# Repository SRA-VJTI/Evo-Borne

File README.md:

# Evoborne
This repository focuses on building an open-source _morphobot_
Autonomous human-friendly Multi-Terrain Scaling Vehicle

## Table of Contents
- Introduction
- Features
- Use Case

## Introduction
EvoBorne is a versatile multi-terrain modular robot designed to adapt to various surface and aerial environments, morphing its structure to meet the demands of its surroundings. It operates as a wheeled robot on land, navigating diverse terrains with speed and agility, and seamlessly transforms into a drone when flight is required. Equipped with advanced mapping techniques and a dynamic morphing capability, EvoBorne can autonomously switch between ground and aerial modes, optimizing performance for complex tasks such as search and rescue, environmental monitoring, and exploration. Its robust, customizable design makes it a powerful tool for overcoming challenging environments.

## Features
### Modular & Adaptive Design

EvoBorne's modular design allows it to easily adapt its structure for different environments and tasks. The design is such that it can be reconfigured, enhancing its versatility and enabling quick transitions between ground and aerial modes.

### Powerful Processing Capabilities

EvoBorne is equipped with powerful processors such as the Jetson Nano that can handle real-time navigation. These capabilities allow the robot to execute complex tasks efficiently, supporting advanced terrain mapping and path-finding operations.

### Multiple Operational Modes

EvoBorne can seamlessly switch between multiple operational modes, functioning as a wheeled robot on land and transforming into a drone when aerial mobility is needed. This flexibility allows it to tackle a variety of tasks in diverse environments.

### Efficient Actuation with Custom ESP32 based custom PCB

The robot's actuation system is controlled by a custom ESP32-based development board, providing efficient and precise control over movement and transformations. This tailored setup enhances responsiveness and overall performance.

### Robust & Precise Flight Control

EvoBorne uses a SpeedyBee flight controller for robust and precise flight control, ensuring stable and reliable aerial operations. This system provides advanced control algorithms that enhance the robot's agility and accuracy during flight.

## Use Case
- EvoBorne is designed to enhance **search and rescue operations** by navigating difficult environments autonomously, using advanced technology to interact with people, and ultimately improving emergency response efficiency. By addressing these issues, EvoBorne could play a vital role in saving lives.
- EvoBorne represents a significant advancement in emergency response technology. Its innovative design and cutting-edge features aim to improve how we handle crises, enabling faster and more efficient assistance in difficult conditions. By reducing the time required to locate and help individuals in danger, EvoBorne could be pivotal in saving lives. Its flexibility and technological sophistication not only make it a valuable tool for rescuers but also push the boundaries of what robots can achieve in real-world scenarios.

## Frameworks & Technologies
- ESP-IDF
- Betaflight
- SolidWorks
- ROS

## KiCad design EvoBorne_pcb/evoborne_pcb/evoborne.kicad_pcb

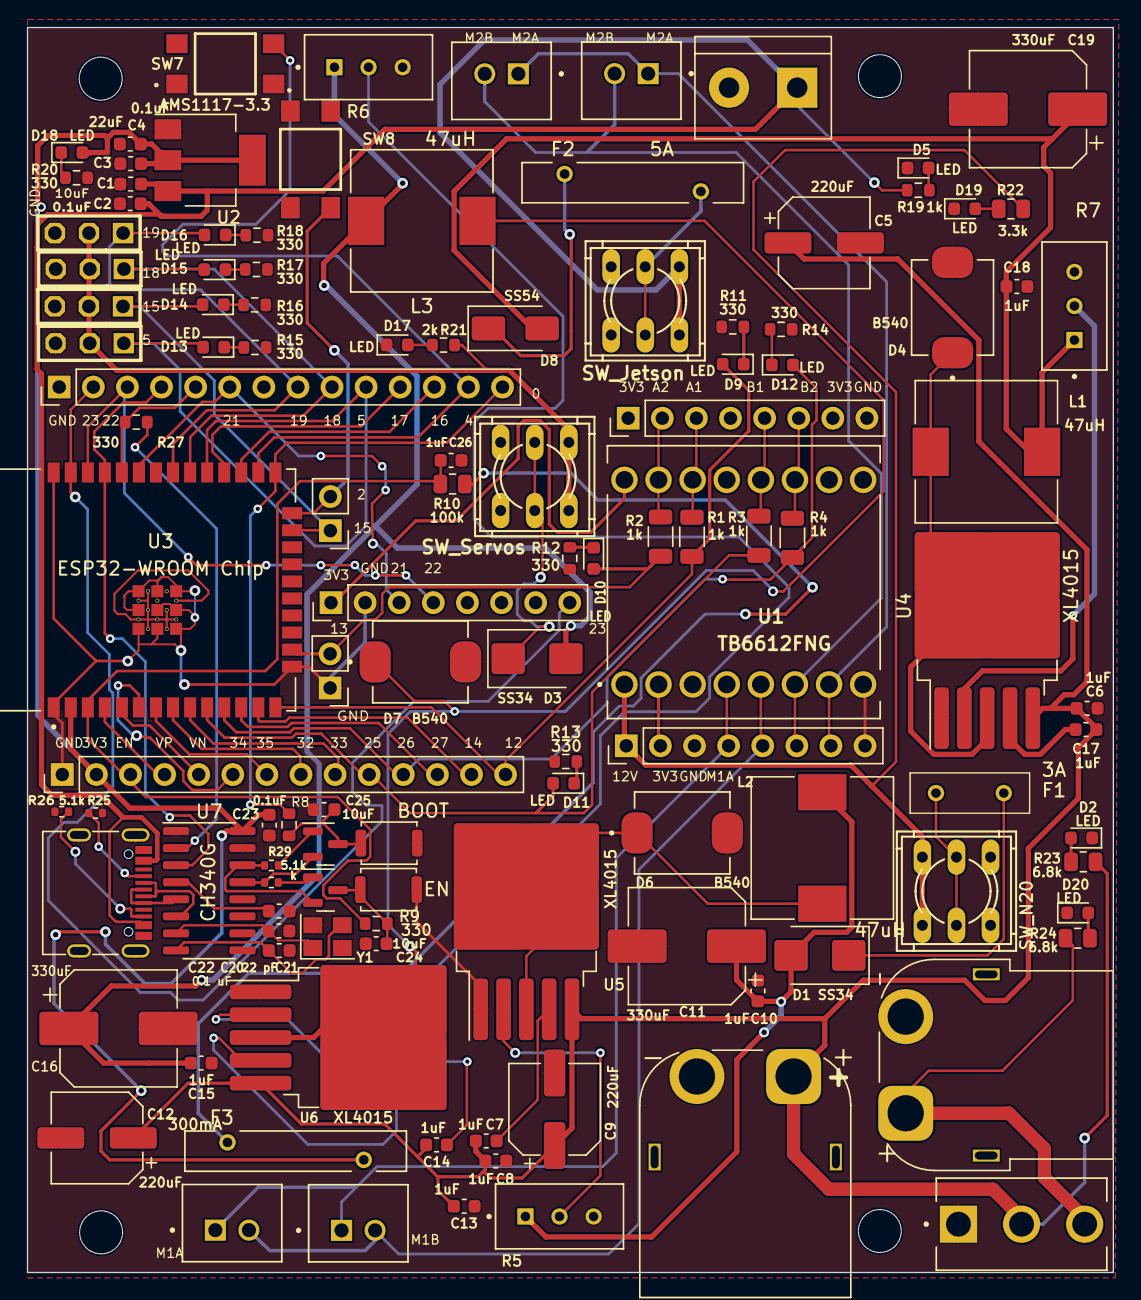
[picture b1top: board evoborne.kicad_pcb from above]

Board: 2 copper layers, 80.9 x 92.7 mm, 122 parts (0 on the bottom side), 88 nets.

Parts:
C1, C24, C25: 10uF; C_0603_1608Metric
C2, C4, C23: 0.1uF; C_0603_1608Metric
C3: 22uF; C_0603_1608Metric
C5, C9, C12: 220uF; CP_Elec_6.3x7.7
C6, C7, C8, C10, C13, C14, C15, C17, C18, C26: 1uF; C_0603_1608Metric
C11, C16, C19: 330uF; CP_Elec_8x10.5
C20, C21: 22 pF; C_0603_1608Metric
C22: 0.1 uF; C_0603_1608Metric
D1, D3: SS34; D_SMB
D2, D5, D9, D10, D11, D12, D13, D14, D15, D16, D17, D18, D19, D20: LED; LED_0603_1608Metric
D4, D6, D7: B540; Diode B540
D8: SS54; D_SMA
F1: 3A; RUEF160
F2: 5A; 5A PTC Fuse RGEF500
F3: 300mA; 1A PTC Fuse RXEF050
H1, H2, H3, H4: MountingHole; MountingHole_3.2mm_M3
J1, J2, J3, J4: B2B-XH-A_LF__SN_; 2 Pin JST
J5, J6, J7, J8: Conn_01x03_Pin; Headers 1X03
J9: XT60; AMASS_XT60PW-M_1x02_P7.20mm_Horizontal
J10: XT60; AMASS_XT60PW-F_1x02_P7.20mm_Horizontal
J11, J12, J15: Conn_01x08_Male; PinHeader_1x08_P2.54mm_Vertical
J13: Screw_Terminal_01x02; TerminalBlock_bornier-2_P5.08mm
J14: USB_C_Receptacle_USB2.0; USB_C_Receptacle_G-Switch_GT-USB-7010ASV
J16, J17: Conn_01x14_Pin; PinHeader_1x14_P2.54mm_Vertical
J18, J19: Conn_01x02_Pin; PinHeader_1x02_P2.54mm_Vertical
L1, L2, L3: 47uH; L_10.4x10.4_H4.8
Q1, Q2: SS8050; SOT-23
R1, R2, R3, R4: 1k; R_1206_3216Metric
R5, R6, R7: TrimPOT 3296; TrimPOT_3296
R8, R9, R11, R12, R13, R14, R15, R16, R17, R18, R20, R27: 330; R_0603_1608Metric
R10: 100k; R_0805_2012Metric
R19: 1k; R_0603_1608Metric
R21: 2k; R_0603_1608Metric
R22: 3.3k; R_0805_2012Metric
R23, R24: 6.8k; R_0805_2012Metric
R25: 5.1 k; R_0402_1005Metric
R26, R28, R29: 5.1k; R_0402_1005Metric
SW1: High Current 3 Pin spdt Switch; 3pin High Current SPDT Switch
SW2: SW_N20; 6 Pin THT Push Switch
SW3: SW_Servos; 6 Pin THT Push Switch
SW4: SW_Jetson; 6 Pin THT Push Switch
SW5: EN; SW_Push_SPST_NO_Alps_SKRK
SW6: BOOT; SW_Push_SPST_NO_Alps_SKRK
SW7, SW8: SW_Push_Dual; Tactile Smd 2x2
U1: TB6612FNG
U2: AMS1117-3.3; SOT-223-3_TabPin2
U3: ESP32-WROOM Chip; ESP32-WROOM-32E__4MB_HIGH_TEMP_CHIP
U4, U5, U6: XL4015; TO-263-5_TabPin3
U7: CH340G; SOIC-16_3.9x9.9mm_P1.27mm
Y1: 12MHz; Crystal_SMD_3225-4Pin_3.2x2.5mm

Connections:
/0: J17.14, R8.2, U3.25 (IO0)
/2: J19.2, SW8.4, U3.24 (IO2)
/3V3: C3.1, C4.1, C23.2, D18.2 (A), F3.1, J11.1, J11.4, J11.7, J12.2, J15.1, J16.2, U1.2 (VCC), U1.10 (PWMB), U1.13 (STBY), U1.16 (PWMA), U2.2 (VO), U3.2 (3V3), U7.16 (VCC)
/3V3_P: F3.2, R10.2
/4: J17.13, SW7.4, U3.26 (IO4)
/5: D13.2 (A), J5.1, J17.10, U3.29 (IO5)
/5V: C18.1, C19.1, D8.2 (A), L1.2, R7.1
/5V_P: C1.1, C2.1, J13.1, J14.A4 (VBUS), J14.A9 (VBUS), J14.B4 (VBUS), J14.B9 (VBUS), R19.1, SW4.3 (C), SW4.6 (C), U2.3 (VI)
/8.4V: C15.1, C16.1, D3.2 (A), L3.2, R6.1
/8.4V_P: J5.2, J6.2, J7.2, J8.2, R21.1, SW3.3 (C), SW3.6 (C)
/12: D9.2 (A), J16.14, R1.1, U3.14 (IO12)
/12V: C10.1, C11.1, D1.2 (A), L2.2, R5.1
/12V_P: J12.1, R22.1, SW2.3 (C), SW2.6 (C), U1.1 (VM)
/13: D10.2 (A), J18.2, R2.1, U3.16 (IO13)
/14: J16.13, U3.13 (IO14)
/15: D14.2 (A), J6.1, J19.1, U3.23 (IO15)
/16: J17.12, U3.27 (IO16)
/17: J17.11, U3.28 (IO17)
/18: D15.2 (A), J7.1, J17.9, U3.30 (IO18)
/19: D16.2 (A), J8.1, J17.8, U3.31 (IO19)
/21: J15.3, J17.6, U3.33 (IO21)
/22: J15.4, J17.3, U3.36 (IO22)
/23: J15.8, J17.2, U3.37 (IO23)
/24V: C5.1, C6.1, C7.1, C8.1, C9.1, C12.1, C13.1, C14.1, C17.1, J9.1 (+), R23.1, SW1.2, U4.5 (VIN), U5.5 (VIN), U6.5 (VIN)
/24V_ESC: J10.1 (+), R24.1, SW1.3
/25: D11.2 (A), J16.10, R3.1, U3.10 (IO25)
/26: D12.2 (A), J16.11, R4.1, U3.11 (IO26)
/27: J16.12, U3.12 (IO27)
/32: J16.8, U3.8 (IO32)
/33: J16.9, U3.9 (IO33)
/34: J16.6, U3.6 (IO34)
/35: J16.7, U3.7 (IO35)
/A1: J11.3, R1.2, U1.14 (AI1)
/A2: J11.2, R2.2, U1.15 (AI2)
/B1: J11.5, R3.2, U1.12 (BI1)
/B2: J11.6, R4.2, U1.11 (BI2)
/EN: C26.1, J16.3, R9.1, R10.1, U3.3 (EN)
/M1A: J1.1, J2.1, J12.4, U1.4 (A01)
/M1B: J1.2, J2.2, J12.5, U1.5 (A02)
/M2A: J3.1, J4.1, J12.7, U1.7 (B01)
/M2B: J3.2, J4.2, J12.6, U1.6 (B02)
/RXD: J17.5, R27.1, U3.34 (RXD0)
/TXD: J17.4, U3.35 (TXD0), U7.3 (RXD)
/VN: J16.5, U3.5 (SENSOR_VN)
/VP: J16.4, U3.4 (SENSOR_VP)
GND: C1.2, C2.2, C3.2, C4.2, C5.2, C6.2, C8.2, C9.2, C10.2, C11.2, C12.2, C13.2, C15.2, C16.2, C18.2, C19.2, C20.2, C21.2, C22.2, C23.1, C24.1, C25.1, C26.2, D2.1 (K), D4.A, D5.1 (K), D6.A, D7.A, D17.1 (K), D19.1 (K), D20.1 (K), J5.3, J6.3, J7.3, J8.3, J9.2 (-), J10.2 (-), J11.8, J12.3, J12.8, J13.2, J14.A1 (GND), J14.A12 (GND), J14.B1 (GND), J14.B12 (GND), J14.S1 (SHIELD), J15.2, J16.1, J17.1, J18.1, R5.3, R6.3, R7.3, R11.2, R12.2, R13.2, R14.2, R15.2, R16.2, R17.2, R18.2, R20.2, R25.2, R26.1, SW1.1, SW5.2, SW6.2, SW7.1, SW7.2, SW8.1, SW8.2, U1.3 (GND), U1.8 (GND), U1.9 (GND), U2.1 (GND), U3.1 (GND), U3.15 (GND), U3.38 (GND), U3.39_1 (GND), U3.39_2 (GND), U3.39_3 (GND), U3.39_4 (GND), U3.39_5 (GND), U3.39_6 (GND), U3.39_7 (GND), U3.39_8 (GND), U3.39_9 (GND), U4.1 (GND), U5.1 (GND), U6.1 (GND), U7.1 (GND), U7.15 (R232), Y1.2, Y1.4
unnamed: D1.1 (K), F1.1
unnamed: D2.2 (A), R23.2
unnamed: D3.1 (K), SW3.2 (B), SW3.5 (B)
unnamed: D5.2 (A), R19.2
unnamed: D8.1 (K), F2.1
unnamed: D9.1 (K), R11.1
unnamed: D10.1 (K), R12.1
unnamed: D11.1 (K), R13.1
unnamed: D12.1 (K), R14.1
unnamed: D13.1 (K), R15.1
unnamed: D14.1 (K), R16.1
unnamed: D15.1 (K), R17.1
unnamed: D16.1 (K), R18.1
unnamed: D17.2 (A), R21.2
unnamed: D18.1 (K), R20.1
unnamed: D19.2 (A), R22.2
unnamed: D20.2 (A), R24.2
unnamed: F1.2, SW2.2 (B), SW2.5 (B)
unnamed: F2.2, SW4.2 (B), SW4.5 (B)
unnamed: J14.A5 (CC1), R25.1
unnamed: J14.B5 (CC2), R26.2
unnamed: Q1.1 (B), R28.1
unnamed: C24.2, Q1.3 (C), R9.2, SW5.1
unnamed: Q1.2 (E), R29.2, U7.14 (~RTS)
unnamed: Q2.1 (B), R29.1
unnamed: C25.2, Q2.3 (C), R8.1, SW6.1
unnamed: Q2.2 (E), R28.2, U7.13 (~DTR)
unnamed: R7.2, U4.2 (FB)
unnamed: D4.C, L1.1, U4.3 (SW)
unnamed: C17.2, U4.4 (VC)
unnamed: R5.2, U5.2 (FB)
unnamed: D6.C, L2.1, U5.3 (SW)
unnamed: C7.2, U5.4 (VC)
unnamed: R6.2, U6.2 (FB)
unnamed: D7.C, L3.1, U6.3 (SW)
unnamed: C14.2, U6.4 (VC)
unnamed: R27.2, U7.2 (TXD)
unnamed: J14.A6 (D+), J14.B6 (D+), U7.5 (UD+)
unnamed: J14.A7 (D-), J14.B7 (D-), U7.6 (UD-)
unnamed: C22.1, U7.4 (V3)
unnamed: C20.1, U7.7 (XI), Y1.1
unnamed: C21.1, U7.8 (XO), Y1.3

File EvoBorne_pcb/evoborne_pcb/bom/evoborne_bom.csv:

"Reference","Value","Datasheet","Footprint","Qty","DNP"
"C1,C24,C25"," 10uF","~","Capacitor_SMD:C_0603_1608Metric","3",""
"C2,C4","0.1uF","~","Capacitor_SMD:C_0603_1608Metric","2",""
"C3","22uF","~","Capacitor_SMD:C_0603_1608Metric","1",""
"C5,C9,C12","220uF","~","Capacitor_SMD:CP_Elec_6.3x7.7","3",""
"C6,C7,C8,C10,C13,C14,C15,C17,C18,C26","1uF","~","Capacitor_SMD:C_0603_1608Metric","10",""
"C11,C16,C19","330uF","~","Capacitor_SMD:CP_Elec_8x10.5","3",""
"C20,C21","22 pF","~","Capacitor_SMD:C_0603_1608Metric","2",""
"C22,C23","0.1 uF","~","Capacitor_SMD:C_0603_1608Metric","2",""
"D1,D3","SS34","http://www.vishay.com/docs/88526/1n5820.pdf","Diode_SMD:D_SMB","2",""
"D2,D5,D9,D10,D11,D12,D13,D14,D15,D16,D17,D18,D19,D20","LED","~","LED_SMD:LED_0603_1608Metric","14",""
"D4,D6,D7","B540","","Diode_SMD:Diode B540","3",""
"D8","SS54","http://www.vishay.com/docs/88526/1n5820.pdf","Diode_SMD:D_SMA","1",""
"F1","3A","~","Fuse:RUEF160","1",""
"F2","5A","~","Fuse:5A PTC Fuse RGEF500","1",""
"H1,H2,H3,H4","MountingHole","~","MountingHole:MountingHole_3.2mm_M3","4",""
"J1,J2,J3,J4","B2B-XH-A_LF__SN_","","Connector:2 Pin JST","4",""
"J5,J6,J7,J8","Conn_01x03_Pin","~","Header Pins:Headers 1X03","4",""
"J9,J10","XT60","","-- mixed values --","2",""
"J11,J12,J15","Conn_01x08_Male","~","Connector_PinHeader_2.54mm:PinHeader_1x08_P2.54mm_Vertical","3",""
"J13","Screw_Terminal_01x02","~","TerminalBlock:TerminalBlock_bornier-2_P5.08mm","1",""
"J14","USB_C_Receptacle_USB2.0","https://www.usb.org/sites/default/files/documents/usb_type-c.zip","Connector_USB:USB_C_Receptacle_G-Switch_GT-USB-7010ASV","1",""
"J16,J17","Conn_01x14_Pin","~","Connector_PinHeader_2.54mm:PinHeader_1x14_P2.54mm_Vertical","2",""
"J18,J19","Conn_01x02_Pin","~","Connector_PinHeader_2.54mm:PinHeader_1x02_P2.54mm_Vertical","2",""
"L1,L2,L3","47uH","~","Inductor_SMD:L_10.4x10.4_H4.8","3",""
"Q1,Q2","SS8050","https://www.fairchildsemi.com/datasheets/2N/2N3904.pdf","Package_TO_SOT_SMD:SOT-23","2",""
"R1,R2,R3,R4,R19","1k","~","-- mixed values --","5",""
"R5,R6,R7","TrimPOT 3296","","Potentiometer_THT:TrimPOT_3296","3",""
"R8,R9,R27","330 ","~","Resistor_SMD:R_0603_1608Metric","3",""
"R10","100k","~","Resistor_SMD:R_0805_2012Metric","1",""
"R11,R12,R13,R14,R15,R16,R17,R18,R20","330","~","Resistor_SMD:R_0603_1608Metric","9",""
"R21","2k","~","Resistor_SMD:R_0603_1608Metric","1",""
"R22","3.3k","~","Resistor_SMD:R_0805_2012Metric","1",""
"R23,R24","6.8k","~","Resistor_SMD:R_0805_2012Metric","2",""
"R25,R26","5.1 k","~","Resistor_SMD:R_0402_1005Metric","2",""
"R28,R29","5.1k","~","Resistor_SMD:R_0402_1005Metric","2",""
"SW1","High Current 3 Pin spdt Switch","","Switches:3pin High Current SPDT Switch","1",""
"SW2","SW_N20","~","Switches:6 Pin THT Push Switch","1",""
"SW3","SW_Servos","~","Switches:6 Pin THT Push Switch","1",""
"SW4","SW_Jetson","~","Switches:6 Pin THT Push Switch","1",""
"SW5","EN","~","Button_Switch_SMD:SW_Push_SPST_NO_Alps_SKRK","1",""
"SW6","BOOT","~","Button_Switch_SMD:SW_Push_SPST_NO_Alps_SKRK","1",""
"SW7,SW8","SW_Push_Dual","~","Switches:Tactile Smd 2x2","2",""
"U1","TB6612FNG","","Motor driver:TB6612FNG","1",""
"U2","AMS1117-3.3","http://www.advanced-monolithic.com/pdf/ds1117.pdf","Package_TO_SOT_SMD:SOT-223-3_TabPin2","1",""
"U3","ESP32-WROOM Chip","","RF_Module:ESP32-WROOM-32E__4MB_HIGH_TEMP_CHIP","1",""
"U4,U5,U6","XL4015","http://www.xlsemi.net/datasheet/XL4015%20datasheet-English.pdf","Package_TO_SOT_SMD:TO-263-5_TabPin3","3",""
"U7","CH340G","http://www.datasheet5.com/pdf-local-2195953","Package_SO:SOIC-16_3.9x9.9mm_P1.27mm","1",""
"Y1","12MHz","~","Crystal:Crystal_SMD_3225-4Pin_3.2x2.5mm","1",""

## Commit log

2024-01-14 Update README.md
    Adds basic overview of the project
2024-04-19 object detection model added
2024-04-19 [ Design ] : Adds Stand for the bot
2024-04-19 [ Design files ] : Adds Stand for the Robot
2024-04-19 [ Design ] : Analysis (PASSING) with FOS 15
2024-04-22 initial servo angle testing
2024-04-22 [MORPHOBOT]: Adds all the cad files
2024-04-22 Morphing Demorphing code
2024-04-23 removed sra board components
2024-04-23 Rewmoved sra board components
2024-04-23 Added sra-board-component as submodule
2024-04-23 Added files
2024-05-20 PCB files updated
2024-07-03 Cleaned up unnecessary files
2024-07-03 Cleaned up unnecessary code
2024-07-03 [UPDATE]: Adds morphing code (#5)
    * initial servo angle testing
    * Morphing Demorphing code
    * removed sra board components
    * Rewmoved sra board components
    * Added sra-board-component as submodule
    * Added sra-board-component as submodule
2024-08-30 [MORPHOBOT]: Adds all the cad files (#6)
2024-08-30 Added code for bldc using dshot-esc
2024-08-30 Adds dshot_esc code (#7)
    * Added code for bldc using dshot-esc
    * Update README.md
2024-08-31 Structuring the repo and add additional files
2024-09-04 Adds documentation , organizes file structure with addition of CAD and PCB design files
2024-09-04 Fixes issue with displaying images
2024-09-05 Adds documentation , firmware and design files in proper directory structure (#8)
    * Structuring the repo and add additional files
    * Adds documentation , organizes file structure with addition of CAD and PCB design files
    * Fixes issue with displaying images
